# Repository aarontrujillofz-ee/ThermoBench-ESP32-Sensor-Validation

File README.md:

# ThermoBench | ESP32 Temperature Sensing & Hardware Validation

**Embedded systems · Analog circuits · PCB design · Python test automation**

ThermoBench is an electrical engineering portfolio project that combines an ESP32 microcontroller, an NTC thermistor, analog signal conditioning, temperature monitoring, simulated fault scenarios, and analysis of real breadboard measurements. This repository provides the **engineering report, design files, source code, calculations, graphs, and test evidence**.

> **Project status:** Physical breadboard measurements documented · KiCad PCB designed but **not fabricated/tested** · LTspice and Wokwi are separate simulation environments · No claim of calibrated temperature accuracy.

## Quick access — find the files

| What you need | Direct link | What it contains |
| --- | --- | --- |
| **Final report** | [23-page PDF](01_Report/ThermoBench_Engineering_Design_and_Validation_Report.pdf) | Start here for the complete project |
| **Circuit schematic** | [View PDF](03_CAD_Visuals/KiCad_Schematic_Original_A4.pdf) | Review the external analog circuit |
| **PCB design** | [KiCad board](02_KiCad_Source/ThermoBench_Sensor_Adapter.kicad_pcb) / [3D render](03_CAD_Visuals/3D_Angled_Original.png) | Designed, not fabricated |
| **ESP32 firmware** | [thermobench.ino](04_Firmware_and_Python/thermobench.ino) | Embedded source code |
| **Python code** | [Python folder](04_Firmware_and_Python/) / [Code walkthrough](docs/firmware-python-guide.md) | Dashboard, CSV parsing and tests |
| **Calculations** | [Worked calculations](docs/calculations.md) | NTC, voltage divider, RC filter, ADC |
| **Graphs and results** | [Thermal response](06_Analysis/thermal_response.png) / [Results guide](docs/results-validation-guide.md) | Physical-recording analysis |
| **Original measurements** | [Four hardware CSV files](05_Hardware_CSV/) | 1,334 archived physical rows |
| **Simulations** | [LTspice](09_LTspice_Simulation/) / [Wokwi](10_Wokwi_Simulation/) | Different virtual models, not physical proof |
| **All project files** | [Complete file index](docs/file-index.md) | Reports, schematics, PCB, code, images, tests and history |

## Project in 60 seconds

**Problem.** Measure temperature using an NTC thermistor and embedded ADC; record the readings and evaluate behavior under different conditions.

**Implementation.** The documented external analog interface uses **R1 = 9.82 kΩ**, **R2 = 990 Ω**, and **C1 = 100 nF** before the ESP32 input at **GPIO34**. The associated PCB design is **50 × 35 mm**.

**Evidence.** The repository separates measurements from a **physical breadboard**, results from **LTspice analog circuit simulations**, and results from a **Wokwi ESP32 simulation**.

**Key limitation.** The Wokwi setup uses a three-pin NTC module with a *built-in divider*. It is **not** a faithful reproduction of the external KiCad R1/R2/C1 input circuit. The designed PCB has not been fabricated or validated on physical hardware.

## Engineering walkthrough

### 1 — Understand the circuit

Start with the [schematic PDF](03_CAD_Visuals/KiCad_Schematic_Original_A4.pdf), then review the [editable KiCad source files](02_KiCad_Source/). The external thermistor divider produces a temperature-dependent voltage that is conditioned before ADC sampling.

### 2 — Review the design calculations

Use the [final report](01_Report/ThermoBench_Engineering_Design_and_Validation_Report.pdf) and [analysis methodology](06_Analysis/Analysis_Methodology.md) for the currently documented analysis. The [worked calculations guide](docs/calculations.md) contains **clearly labeled worked examples** for the divider equation, NTC conversion, ADC scaling, and analog filter, with inputs, units, assumptions, and calculations independently checked against the implemented design. Do not substitute unverified theoretical results for measured data.

### 3 — Explore the PCB

Open the [KiCad project](02_KiCad_Source/ThermoBench_Sensor_Adapter.kicad_pro), [PCB source](02_KiCad_Source/ThermoBench_Sensor_Adapter.kicad_pcb), and [3D view](03_CAD_Visuals/3D_Angled_Original.png). **Design files are not evidence of a manufactured or tested PCB.**

### 4 — Follow the firmware and Python workflow

Read [BUILD_STEPS.md](04_Firmware_and_Python/BUILD_STEPS.md) first. Review the [ESP32 sketch](04_Firmware_and_Python/thermobench.ino), [dashboard.py](04_Firmware_and_Python/dashboard.py), and [requirements.txt](04_Firmware_and_Python/requirements.txt). Hardware and Python requirements depend on which part of the project you want to reproduce.

### 5 — Inspect measured results

Review the [original breadboard CSV recordings](05_Hardware_CSV/), [analysis methodology](06_Analysis/Analysis_Methodology.md), and figures below. The graphs are presented as analysis outputs, not proof of external calibration accuracy.

### 6 — Review simulation evidence separately

- [LTspice original circuit files and validation figures](09_LTspice_Simulation/) — analog circuit modeling.
- [Wokwi test procedures](10_Wokwi_Simulation/WOKWI_TEST_CASES.md) and [observed evidence](10_Wokwi_Simulation/Evidence/) — firmware behavior in a different simulated circuit configuration.

For the documented Wokwi firmware, the `HOT` state activates at **45°C** and clears at **43°C**. The available evidence includes selected transcribed simulator logs, not a full exported run. See the [verified Wokwi figure](10_Wokwi_Simulation/Figures/Wokwi_Hysteresis_Verified.png).

## What was verified — and what remains open

| Area | Evidence status |
|---|---|
| Breadboard sensing and recorded measurements | Physical measurement files included |
| KiCad schematic and board layout | Design files and render included |
| Manufactured PCB and assembled-board performance | **Not completed** |
| LTspice analog circuit response | Simulation evidence included |
| Wokwi alarm behavior | Selected simulator observations included |
| Independently calibrated absolute temperature accuracy | **Not established** |
| Preliminary Gerber exports | **Not for manufacturing**; see [notice](07_Reference_Exports/Preliminary_Gerbers/NOT_FOR_MANUFACTURING.txt) |
| Synthetic example data | Explicitly separated under [Synthetic Demo Only](08_Synthetic_Demo_Only/) |

## Notes and source provenance

This project was developed with **AI assistance** for portions of documentation and supporting scripts; the underlying source and recorded evidence are supplied for inspection. Do not interpret model output, simulated data, or design-only PCB files as verified physical results.

For the historical package map, see [README_START_HERE.md](README_START_HERE.md). For images and references, see [FIGURES_AND_SCHEMATICS_INDEX.md](FIGURES_AND_SCHEMATICS_INDEX.md).

**Reuse rights:** This public portfolio repository does not currently grant an explicit reuse license. Review any private metadata or logs before publishing updates.

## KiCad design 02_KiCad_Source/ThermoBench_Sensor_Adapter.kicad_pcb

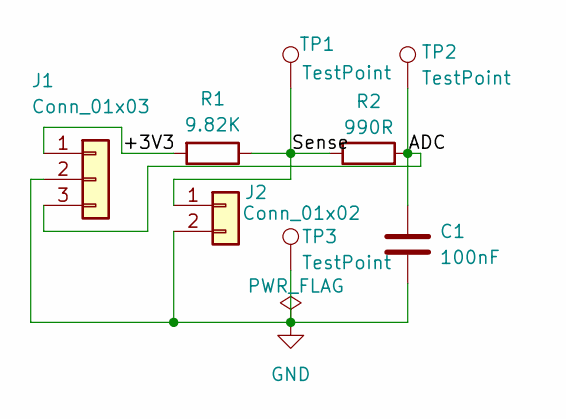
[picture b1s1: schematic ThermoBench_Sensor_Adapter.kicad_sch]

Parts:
C1: 100nF; C_Disc_D4.7mm_W2.5mm_P5.00mm
J1: Conn_01x03; PinHeader_1x03_P2.54mm_Vertical
J2: Conn_01x02; PinHeader_1x02_P2.54mm_Vertical
R1: 9.82K; R_Axial_DIN0207_L6.3mm_D2.5mm_P7.62mm_Horizontal
R2: 990R; R_Axial_DIN0207_L6.3mm_D2.5mm_P7.62mm_Horizontal
TP1, TP2, TP3: TestPoint; TestPoint_THTPad_D2.0mm_Drill1.0mm

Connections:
/+3V3: J1.1, R1.2
/ADC: C1.1, J1.3, R2.2, TP2.1 (1_1)
/Sense: J2.1, R1.1, R2.1, TP1.1 (1_1)
GND: C1.2, J1.2, J2.2, TP3.1 (1_1)

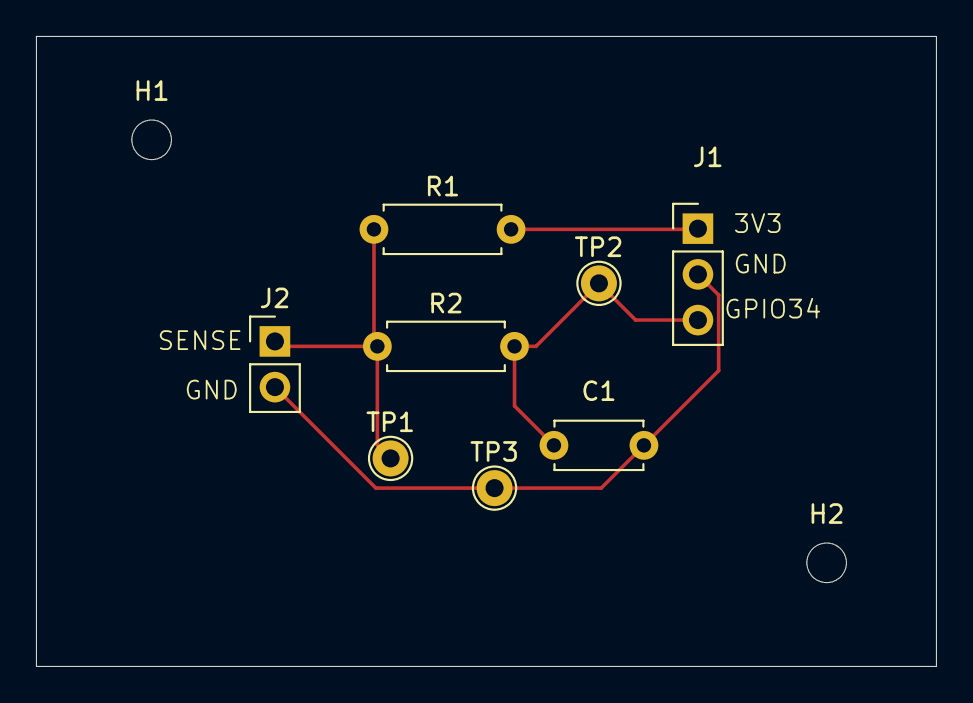
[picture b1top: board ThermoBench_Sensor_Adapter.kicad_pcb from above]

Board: 2 copper layers, 50.0 x 35.0 mm, 10 parts (0 on the bottom side), 4 nets.

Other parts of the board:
H1, H2: MountingHole_2.2mm_M2_ISO7380
